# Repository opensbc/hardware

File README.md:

# hardware
The PCB and hardware design for the opensbc project

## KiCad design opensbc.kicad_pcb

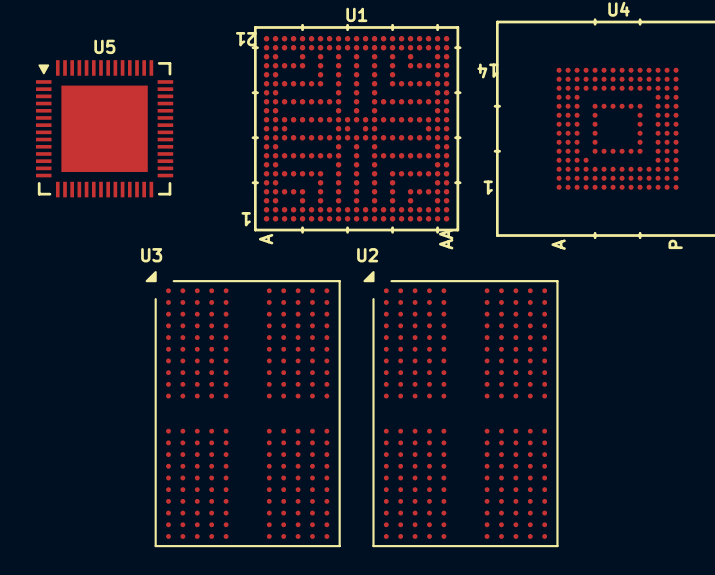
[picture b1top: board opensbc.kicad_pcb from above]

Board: 8 copper layers, 5 parts (0 on the bottom side), 8 nets, no tracks yet.

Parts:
U1: MIMX8MN5DVPIZDA; FCBGA-306
U2, U3: B3221PM3BDGUI; BGA-200_10.0x14.5mm_Layout12x22_P0.80x0.65mm
U4: EMMC32G-TS0A-01002; FBGA153_13X11.5X0.8
U5: PCA9450BHNY; HVQFN56

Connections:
GND: U1.A1 (VSS), U1.A21 (VSS), U1.AA1 (VSS), U1.AA21 (VSS), U1.B20 (VSS), U1.C4 (VSS), U1.C6 (VSS), U1.C8 (VSS), U1.C10 (VSS), U1.C12 (VSS), U1.C14 (VSS), U1.C16 (VSS), U1.C18 (VSS), U1.E3 (VSS), U1.E19 (VSS), U1.G3 (VSS), U1.G19 (VSS), U1.H8 (VSS), U1.H10 (VSS), U1.H12 (VSS), U1.H14 (VSS), U1.J3 (VSS), U1.J8 (VSS), U1.J14 (VSS), U1.J19 (VSS), U1.K11 (VSS), U1.L3 (VSS), U1.L8 (VSS), U1.L14 (VSS), U1.L19 (VSS), U1.M11 (VSS), U1.N3 (VSS), U1.N8 (VSS), U1.N14 (VSS), U1.N19 (VSS), U1.P8 (VSS), U1.P10 (VSS), U1.P12 (VSS), U1.P14 (VSS), U1.R3 (VSS), U1.R19 (VSS), U1.U3 (VSS), U1.U19 (VSS), U1.W4 (VSS), U1.W6 (VSS), U1.W8 (VSS), U1.W10 (VSS), U1.W12 (VSS), U1.W14 (VSS), U1.W16 (VSS), U1.W18 (VSS), U2.A3 (VSS), U2.A10 (VSS), U2.AB3 (VSS), U2.AB5 (VSS), U2.AB8 (VSS), U2.AB10 (VSS), U2.C1 (VSS), U2.C5 (VSS), U2.C8 (VSS), U2.C12 (VSS), U2.D2 (VSS), U2.D4 (VSS), U2.D9 (VSS), U2.D11 (VSS), U2.E1 (VSS), U2.E5 (VSS), U2.E8 (VSS), U2.E12 (VSS), U2.G1 (VSS), U2.G3 (VSS), U2.G5 (VSS), U2.G8 (VSS), U2.G10 (VSS), U2.G12 (VSS), U2.J1 (VSS), U2.J3 (VSS), U2.J10 (VSS), U2.J12 (VSS), U2.K2 (VSS), U2.K4 (VSS), U2.K9 (VSS), U2.K11 (VSS), U2.N2 (VSS), U2.N4 (VSS), U2.N9 (VSS), U2.N11 (VSS), U2.P1 (VSS), U2.P3 (VSS), U2.P10 (VSS), U2.P12 (VSS), U2.T1 (VSS), U2.T3 (VSS), U2.T5 (VSS), U2.T8 (VSS), U2.T10 (VSS), U2.T12 (VSS), U2.V1 (VSS), U2.V5 (VSS), U2.V8 (VSS), U2.V12 (VSS), U2.W2 (VSS), U2.W4 (VSS), U2.W9 (VSS), U2.W11 (VSS), U2.Y1 (VSS), U2.Y5 (VSS), U2.Y8 (VSS), U2.Y12 (VSS), U3.A3 (VSS), U3.A10 (VSS), U3.AB3 (VSS), U3.AB5 (VSS), U3.AB8 (VSS), U3.AB10 (VSS), U3.C1 (VSS), U3.C5 (VSS), U3.C8 (VSS), U3.C12 (VSS), U3.D2 (VSS), U3.D4 (VSS), U3.D9 (VSS), U3.D11 (VSS), U3.E1 (VSS), U3.E5 (VSS), U3.E8 (VSS), U3.E12 (VSS), U3.G1 (VSS), U3.G3 (VSS), U3.G5 (VSS), U3.G8 (VSS), U3.G10 (VSS), U3.G12 (VSS), U3.J1 (VSS), U3.J3 (VSS), U3.J10 (VSS), U3.J12 (VSS), U3.K2 (VSS), U3.K4 (VSS), U3.K9 (VSS), U3.K11 (VSS), U3.N2 (VSS), U3.N4 (VSS), U3.N9 (VSS), U3.N11 (VSS), U3.P1 (VSS), U3.P3 (VSS), U3.P10 (VSS), U3.P12 (VSS), U3.T1 (VSS), U3.T3 (VSS), U3.T5 (VSS), U3.T8 (VSS), U3.T10 (VSS), U3.T12 (VSS), U3.V1 (VSS), U3.V5 (VSS), U3.V8 (VSS), U3.V12 (VSS), U3.W2 (VSS), U3.W4 (VSS), U3.W9 (VSS), U3.W11 (VSS), U3.Y1 (VSS), U3.Y5 (VSS), U3.Y8 (VSS), U3.Y12 (VSS), U4.A6 (VSS), U4.C4 (VSS_q), U4.E7 (VSS), U4.G5 (VSS), U4.H10 (VSS), U4.J5 (VSS), U4.K8 (VSS), U4.N2 (VSS_q), U4.N5 (VSS_q), U4.P4 (VSS_q), U4.P6 (VSS_q)
NVCC_DRAM: U1.G6 (NVCC_DRAM), U1.J6 (NVCC_DRAM), U1.J7 (NVCC_DRAM), U1.L6 (NVCC_DRAM), U1.N6 (NVCC_DRAM), U1.N7 (NVCC_DRAM), U1.R6 (NVCC_DRAM)
VCC: U4.E6 (VCC), U4.F5 (VCC), U4.J10 (VCC), U4.K9 (VCC)
VCC_q: U4.C6 (VCC_q), U4.M4 (VCC_q), U4.N4 (VCC_q), U4.P3 (VCC_q), U4.P5 (VCC_q)
VDD1: U2.F1 (VDD1), U2.F12 (VDD1), U2.G4 (VDD1), U2.G9 (VDD1), U2.T4 (VDD1), U2.T9 (VDD1), U2.U1 (VDD1), U2.U12 (VDD1), U3.F1 (VDD1), U3.F12 (VDD1), U3.G4 (VDD1), U3.G9 (VDD1), U3.T4 (VDD1), U3.T9 (VDD1), U3.U1 (VDD1), U3.U12 (VDD1)
VDD2: U2.A4 (VDD2), U2.A9 (VDD2), U2.AB4 (VDD2), U2.AB9 (VDD2), U2.F5 (VDD2), U2.F8 (VDD2), U2.H1 (VDD2), U2.H5 (VDD2), U2.H8 (VDD2), U2.H12 (VDD2), U2.K1 (VDD2), U2.K3 (VDD2), U2.K10 (VDD2), U2.K12 (VDD2), U2.N1 (VDD2), U2.N3 (VDD2), U2.N10 (VDD2), U2.N12 (VDD2), U2.R1 (VDD2), U2.R5 (VDD2), U2.R8 (VDD2), U2.R12 (VDD2), U2.U5 (VDD2), U2.U8 (VDD2), U3.A4 (VDD2), U3.A9 (VDD2), U3.AB4 (VDD2), U3.AB9 (VDD2), U3.F5 (VDD2), U3.F8 (VDD2), U3.H1 (VDD2), U3.H5 (VDD2), U3.H8 (VDD2), U3.H12 (VDD2), U3.K1 (VDD2), U3.K3 (VDD2), U3.K10 (VDD2), U3.K12 (VDD2), U3.N1 (VDD2), U3.N3 (VDD2), U3.N10 (VDD2), U3.N12 (VDD2), U3.R1 (VDD2), U3.R5 (VDD2), U3.R8 (VDD2), U3.R12 (VDD2), U3.U5 (VDD2), U3.U8 (VDD2)
VDDQ: U2.AA3 (VDDQ), U2.AA5 (VDDQ), U2.AA8 (VDDQ), U2.AA10 (VDDQ), U2.B3 (VDDQ), U2.B5 (VDDQ), U2.B8 (VDDQ), U2.B10 (VDDQ), U2.D1 (VDDQ), U2.D5 (VDDQ), U2.D8 (VDDQ), U2.D12 (VDDQ), U2.F3 (VDDQ), U2.F10 (VDDQ), U2.U3 (VDDQ), U2.U10 (VDDQ), U2.W1 (VDDQ), U2.W5 (VDDQ), U2.W8 (VDDQ), U2.W12 (VDDQ), U3.AA3 (VDDQ), U3.AA5 (VDDQ), U3.AA8 (VDDQ), U3.AA10 (VDDQ), U3.B3 (VDDQ), U3.B5 (VDDQ), U3.B8 (VDDQ), U3.B10 (VDDQ), U3.D1 (VDDQ), U3.D5 (VDDQ), U3.D8 (VDDQ), U3.D12 (VDDQ), U3.F3 (VDDQ), U3.F10 (VDDQ), U3.U3 (VDDQ), U3.U10 (VDDQ), U3.W1 (VDDQ), U3.W5 (VDDQ), U3.W8 (VDDQ), U3.W12 (VDDQ)
VDD_SOC: U1.J9 (VDD_SOC), U1.J10 (VDD_SOC), U1.J11 (VDD_SOC), U1.J12 (VDD_SOC), U1.J13 (VDD_SOC), U1.K10 (VDD_SOC), U1.K12 (VDD_SOC), U1.L9 (VDD_SOC), U1.L10 (VDD_SOC), U1.L12 (VDD_SOC), U1.L13 (VDD_SOC), U1.M10 (VDD_SOC), U1.M12 (VDD_SOC), U1.N9 (VDD_SOC), U1.N10 (VDD_SOC), U1.N11 (VDD_SOC), U1.N12 (VDD_SOC), U1.N13 (VDD_SOC)

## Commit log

2025-04-01 Imported parts
2025-04-26 Schematic progress
2025-04-26 Revert "Schematic progress"
    This reverts commit 0ab4f18268ae0280199bb3a3efdd6a38bd66ed97.
